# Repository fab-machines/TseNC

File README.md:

<div align="center"><h1 style=align="center">TseNC</h1></div>

<div align="center"></div>
<div align="center"><i>Open Source CNC Milling Machine</i></div>

TseNC specifications
--

- working area: 600x370x145mm Y-X-Z (400mm on X with no side protection)
- frame: solid aluminum plates of 6/8/12/20mm bolted
- Bed: aluminum nut profiled Nut 8
- actuators: 16mm ballscrews on X and Y, 12mm ballscrew on Z
- linear guides: Hiwin HGR15
- maximum speed: 4000mm/min
- mechanical resolution: 0.003125mm
- spindle: Mafell FM1000 1Kw
- firmware: GRBL-LPC
- controller: LPC1768 32bit
- motors: NEMA 24 4MN
- motor controllers: 3 x DM556
- compatible collets: 3/4/5/6/8mm 1/8 and 1/4
- quick spindle release
- Z zero sensor
- inductive endstops with softlimits
- side procection of 6mm POM
- emergency button with fuse protection

Author
--
Project Lead:<br>
Prof. Dr. William Megill<br>
Prof. Dr. Karsten Nebe
<br>
<br>
Machine design and fabrication:<br>
Daniele Ingrassia
<br>
<br>
Technical help and assembly:<br>
Leen Nijim<br>
Kevin Brinkmann<br>
<br>
Rhine-Waal University of Applied Sciences<br>
https://www.hochschule-rhein-waal.de/en

License
--

TseNC and all the work in this repository is released under the following open source license:

CERN Open Hardware Licence - Weakly Reciprocal, CERN-OHL-W

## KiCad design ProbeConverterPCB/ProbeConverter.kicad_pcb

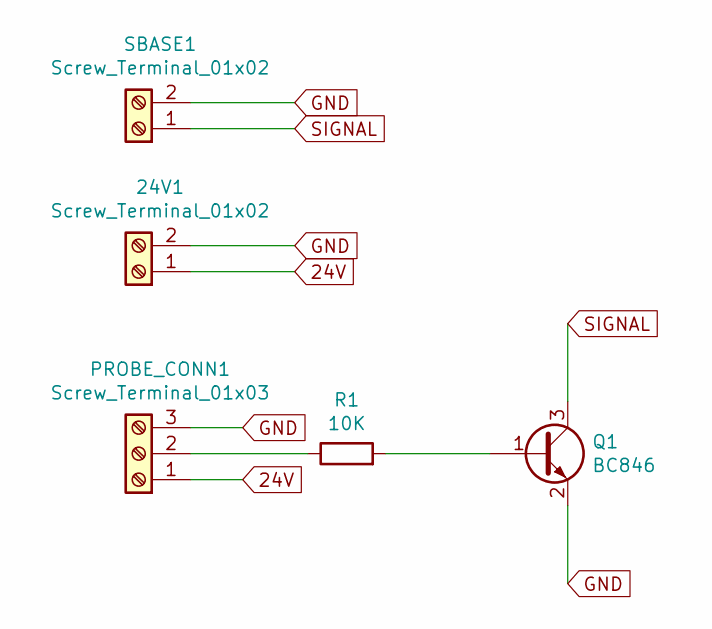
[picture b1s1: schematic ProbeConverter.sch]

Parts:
24V1: Screw_Terminal_01x02; TerminalBlock_bornier-2_P5.08mm
PROBE_CONN1: Screw_Terminal_01x03; TerminalBlock_bornier-3_P5.08mm
Q1: BC846; SOT-23
R1: 10K; R_1206
SBASE1: Screw_Terminal_01x02; TerminalBlock_bornier-2_P5.08mm

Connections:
24V: 24V1.1, PROBE_CONN1.1
GND: 24V1.2, PROBE_CONN1.3, Q1.2 (E), SBASE1.2
unnamed: PROBE_CONN1.2, R1.1
unnamed: Q1.1 (B), R1.2
SIGNAL: Q1.3 (C), SBASE1.1

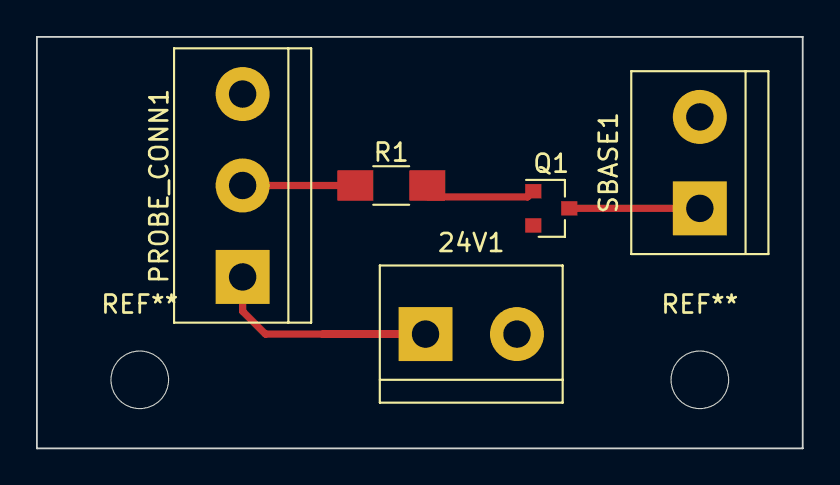
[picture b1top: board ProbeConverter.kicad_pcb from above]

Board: 2 copper layers, 42.5 x 22.9 mm, 5 parts (0 on the bottom side), 5 nets.

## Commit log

2021-06-22 initial commit, added some details to README
2021-06-22 added some details to README
2021-07-05 Add files via upload
    added initial 3D design
2021-07-05 Add files via upload
    added initial BOM
2021-08-23 Add files via upload
    added 3D models
2021-09-06 added probe converter pcb
